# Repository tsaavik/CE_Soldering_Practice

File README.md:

CE_Soldering_Practice
=====================

A board for learning how to solder without breaking anything.

Since we are soldering componets to a board, might as well power them and turn them into breakout boards

Design Requirements
===================

1. variety of surface mount passive components (sizes, not types — 0603, 0805, etc)
1. MSOP
1. TSSOP
1. SOIC
1. Through hole components
1. A part with a large power pad (can be combined with one of the other listed parts)

Click image to enlarge

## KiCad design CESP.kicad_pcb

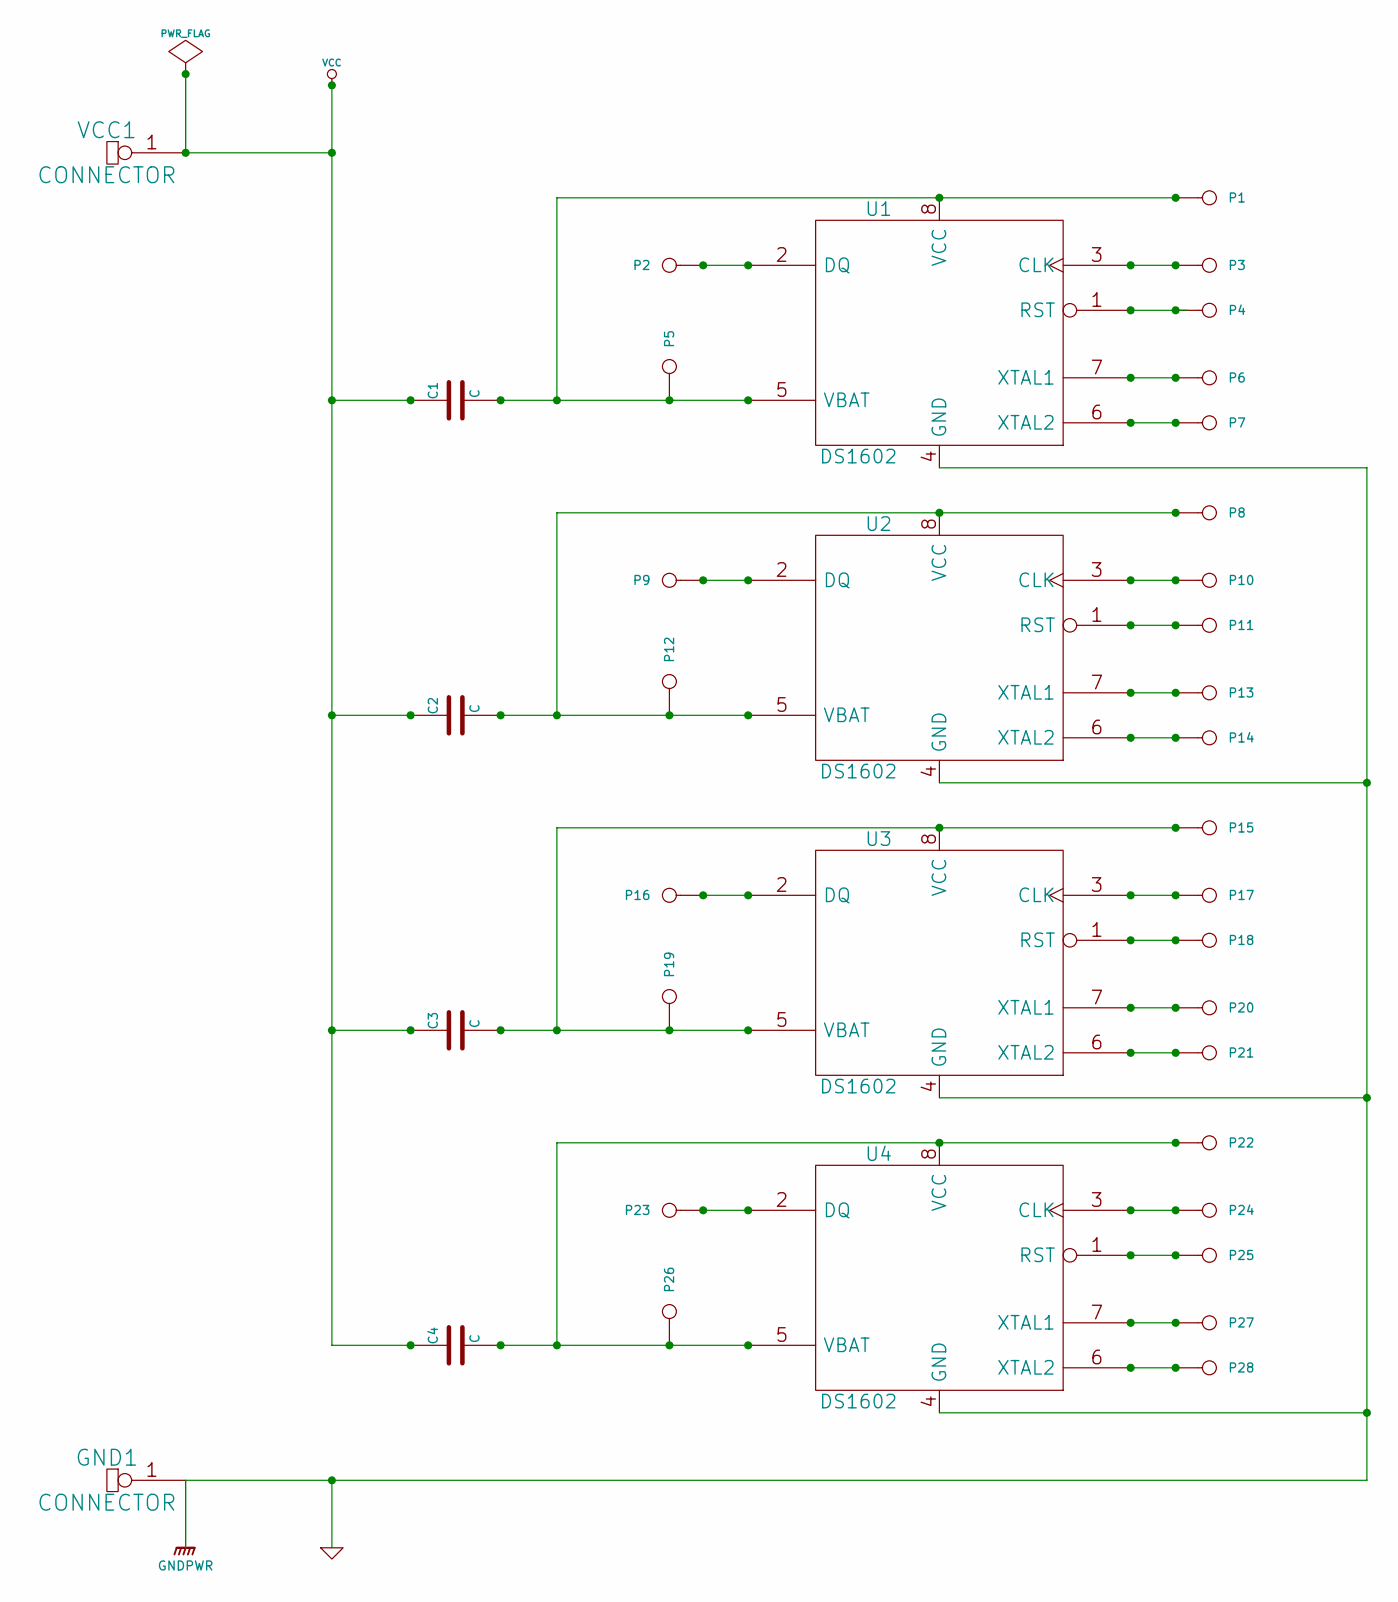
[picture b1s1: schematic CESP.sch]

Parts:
C1, C2, C3, C4: C
GND1: CONNECTOR
P1, P2, P3, P4, P5, P6, P7, P8, P9, P10, P11, P12, P13, P14, P15, P16, P17, P18, P19, P20, P21, P22, P23, P24, P25, P26, P27, P28: CONN_1
U1, U2, U3, U4: DS1602
VCC1: CONNECTOR

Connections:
GND: GND1.1, U1.4 (GND), U2.4 (GND), U3.4 (GND), U4.4 (GND)
unnamed: P13.1, U2.7 (XTAL1)
unnamed: P21.1, U3.6 (XTAL2)
unnamed: P14.1, U2.6 (XTAL2)
unnamed: P11.1, U2.1 (RST)
unnamed: P10.1, U2.3 (CLK)
unnamed: P20.1, U3.7 (XTAL1)
unnamed: P17.1, U3.3 (CLK)
unnamed: P18.1, U3.1 (RST)
unnamed: P23.1, U4.2 (DQ)
unnamed: P16.1, U3.2 (DQ)
unnamed: P28.1, U4.6 (XTAL2)
unnamed: P27.1, U4.7 (XTAL1)
unnamed: P25.1, U4.1 (RST)
unnamed: P24.1, U4.3 (CLK)
unnamed: P3.1, U1.3 (CLK)
unnamed: P6.1, U1.7 (XTAL1)
unnamed: P7.1, U1.6 (XTAL2)
unnamed: C1.2, P1.1, P5.1, U1.5 (VBAT), U1.8 (VCC)
unnamed: P4.1, U1.1 (RST)
unnamed: P9.1, U2.2 (DQ)
unnamed: P2.1, U1.2 (DQ)
unnamed: C2.2, P8.1, P12.1, U2.5 (VBAT), U2.8 (VCC)
unnamed: C3.2, P15.1, P19.1, U3.5 (VBAT), U3.8 (VCC)
unnamed: C4.2, P22.1, P26.1, U4.5 (VBAT), U4.8 (VCC)
VCC: C1.1, C2.1, C3.1, C4.1, VCC1.1

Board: 2 copper layers, 36 parts (0 on the bottom side), 26 nets, no tracks yet.

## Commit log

2014-01-26 Somewhat working version, still have some errors
2014-01-26 New generated files, and a screenshot for forum
2014-01-26 better picture
2014-01-26 Update README.md
    added pic
2014-01-26 Update README.md
    added help text to readme
